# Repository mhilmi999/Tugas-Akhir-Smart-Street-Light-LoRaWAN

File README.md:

# Documentation Presentation
## Final Project of Bachelor Degree
[View the Presentation](https://docs.google.com/presentation/d/1WL7GJ676_46_-2-AJBF_TlKwIyaG7xFXZGKN8_uwHc8/edit?usp=sharing)

## International Journal ISITIA 2023
[See the Conference](https://docs.google.com/presentation/d/11-YCotPrYtim7DABWWCKuuAZa3wxNNcI8QoDBYtIVPg/edit?usp=sharing)

## Certificate 
[Authors](https://github.com/mhilmi999/Tugas-Akhir-Smart-Street-Light-LoRaWAN/blob/main/ISITIA2023-Hilmi_Authors.pdf)
[Presenter](https://github.com/mhilmi999/Tugas-Akhir-Smart-Street-Light-LoRaWAN/blob/main/ISITIA2023-Hilmi_Presenter.pdf)

## Hal-hal yang dibutuhkan
- Bahasa Pemrograman Go [Go official website](https://go.dev/)
- Pengetahuan atas [Gin Framework](https://gin-gonic.com/)
- Pemahaman implementasi MySQL yang terimplementasi oleh [GORM](https://gorm.io/)
- Sistem folder yang berbasis code base [Clean Architecture](https://medium.com/golangid/mencoba-golang-clean-architecture-c2462f355f41)
- CSS yang dibangun dengan integrasi [Bootstrap 5](https://getbootstrap.com/docs/5.0/getting-started/introduction/)

## Instalasi dan Menjalankan Sistem Aplikasi
- Unduh dan [Clone repository](https://github.com/mhilmi999/Tugas-Akhir-Smart-Street-Light-LoRaWAN.git) ini pada IDE kesayangan Anda
- Pastikan Go telah terinstall pada perangkat anda, hal ini d
apat dilakukan dengan command (Contoh dengan Mac):
    ```
    go --version 
    ```
- Lanjutkan dengan melakukan import database [Smartstreetlighrt.sql](sql/smartstreetlight.sql) pada database adminer (phpmyadmin/mariadb/dbeaver) Anda.
- Pastikan Anda berada pada path dimana project berada ketika ingin menjalankannya berikut contohnya: 
    ```
    mhilmi@mhilmis-MacBook-Pro Tugas-Akhir-Smart-Street-Light-LoRaWAN % pwd
    /Users/mhilmi/Documents/golangProject/src/github.com/mhilmi999/Tugas-Akhir-Smart-Street-Light-LoRaWAN
    mhilmi@mhilmis-MacBook-Pro Tugas-Akhir-Smart-Street-Light-LoRaWAN % 
    ```
- Jalankan auto download library aplikasi dengan command:
    ```
    go mod init
    go mod vendor
    go mod tidy
    ```
- Jalankan aplikasi dengan command:
    ```
    go run main.go
    ```
- Buka browser dan ketikan pada url
    ```
    localhost:9999
    ```
- Setelah sukses seharusnya tampil laman login dengan:
    ```
    username    : hilmi@email.com
    password    : 12345
    ```
    
- Berikut merupakan tampilan awal ketika mencapai dashboard yang dibangun
    
- Tampilan laman list perangkat

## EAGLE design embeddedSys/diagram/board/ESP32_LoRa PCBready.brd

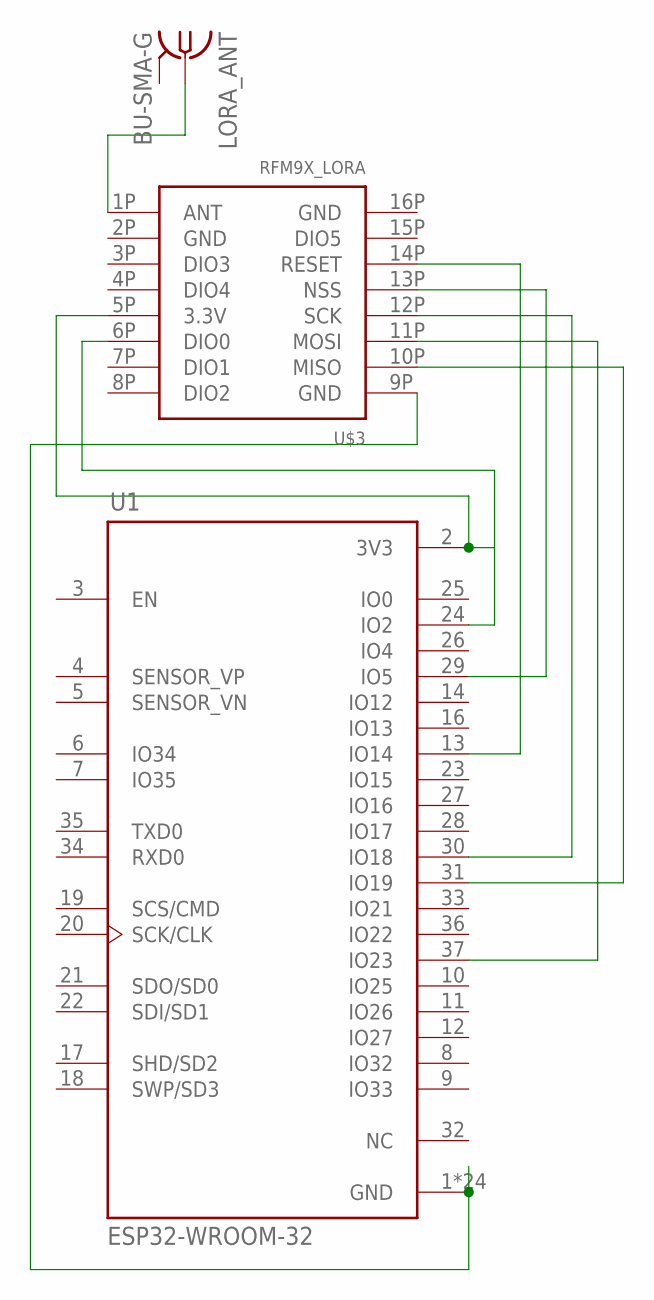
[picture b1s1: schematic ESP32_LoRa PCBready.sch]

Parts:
LORA_ANT: BU-SMA-G
U1: ESP32-WROOM-32; MODULE_ESP32-WROOM-32
U$3: RFM9X_LORA; RFM9X_SMT

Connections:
unnamed: U1.2 (3V3), U$3.5P (3.3V)
unnamed: LORA_ANT.1, U$3.1P (ANT)
unnamed: U1.1 (GND), U1.15 (GND), U1.38 (GND), U1.39_1 (GND), U1.39_2 (GND), U1.39_3 (GND), U1.39_4 (GND), U1.39_5 (GND), U1.39_6 (GND), U1.39_7 (GND), U1.39_8 (GND), U1.39_9 (GND), U1.39_10 (GND), U1.39_11 (GND), U1.39_12 (GND), U1.39_13 (GND), U1.39_14 (GND), U1.39_15 (GND), U1.39_16 (GND), U1.39_17 (GND), U1.39_18 (GND), U1.39_19 (GND), U1.39_20 (GND), U1.39_21 (GND), U$3.9P (GND)
unnamed: U1.24 (IO2), U$3.6P (DIO0)
unnamed: U1.13 (IO14), U$3.14P (RESET)
unnamed: U1.29 (IO5), U$3.13P (NSS)
unnamed: U1.30 (IO18), U$3.12P (SCK)
unnamed: U1.37 (IO23), U$3.11P (MOSI)
unnamed: U1.31 (IO19), U$3.10P (MISO)

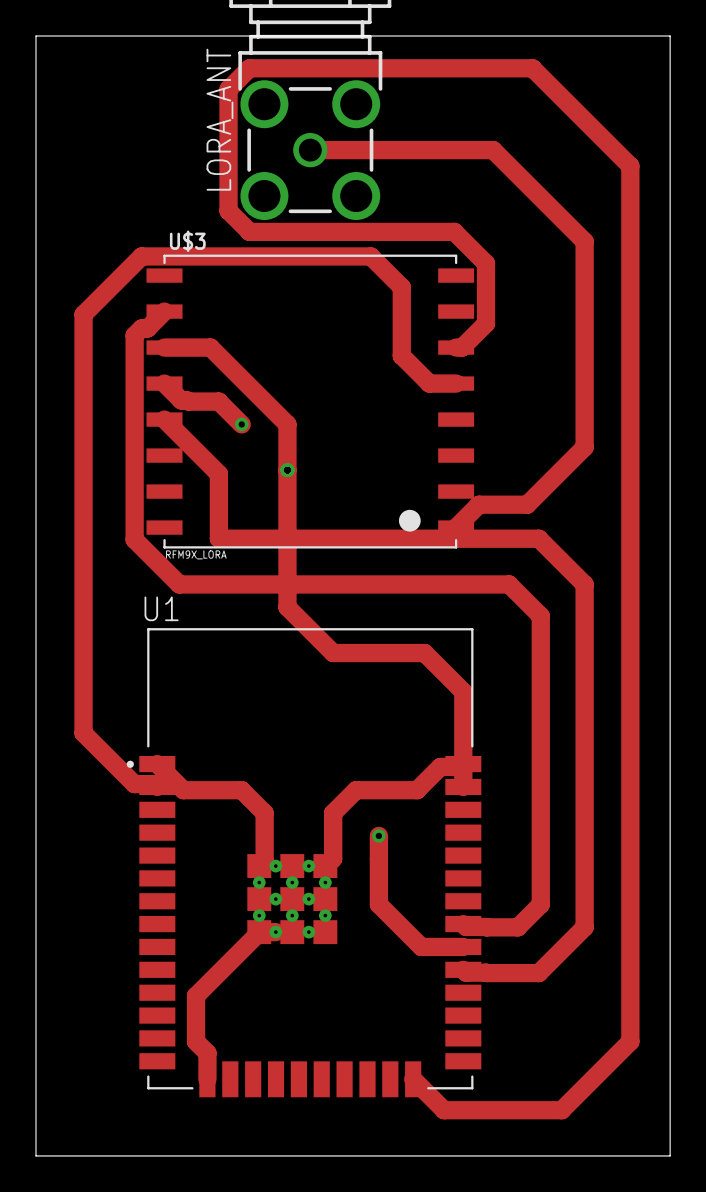
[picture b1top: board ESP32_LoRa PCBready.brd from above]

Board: 2 copper layers, 35.2 x 62.2 mm, 3 parts (0 on the bottom side), 9 nets.

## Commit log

2022-10-25 Initialize Codebase for T.A SmartStreetLight
2022-10-26 fix run the base code and connected into front end
2022-10-26 Fix solving connected html, Gin, Gorm Golang
2022-11-06 Adding examples for sensor, actuator, and fix LoRa
2022-11-20 fixing embedded system pzem sensor codes
2022-11-20 Add a base template
2022-11-20 Improvement for dynamic template, login, and register feature
2022-11-20 Fix Login cookie session store
2022-11-21 Adding middlewares login session and logout func
2022-11-26 big updates for layout and embedded system code
2022-11-28 scratch webhook and get latest data antares
2022-11-28 Update payload lora sent and saved struct GET http
2022-11-29 Fix split data sent from antares and embedded
2022-11-29 Cleans up the multiple layering and library unused
2022-11-30 Fix saved from API GET and FE chart dashboard
2022-11-30 table list device done
2022-11-30 webhook receiver done
2022-12-04 imrovement for Downlink command and post antares
2022-12-04 fix final web apps control light on/off
2022-12-05 Web done primary feature
2022-12-09 adding mqtt python subscriber
2022-12-09 Update webhook monitoring
2022-12-10 adding mqtt subs with go routine
2022-12-10 MQTT Monitoring Done
2023-01-01 Fix controll embedded system lamp and mqtt protocols
2023-01-05 Fix bug and donwlink command
2023-02-03 User Guidance Next re-production
